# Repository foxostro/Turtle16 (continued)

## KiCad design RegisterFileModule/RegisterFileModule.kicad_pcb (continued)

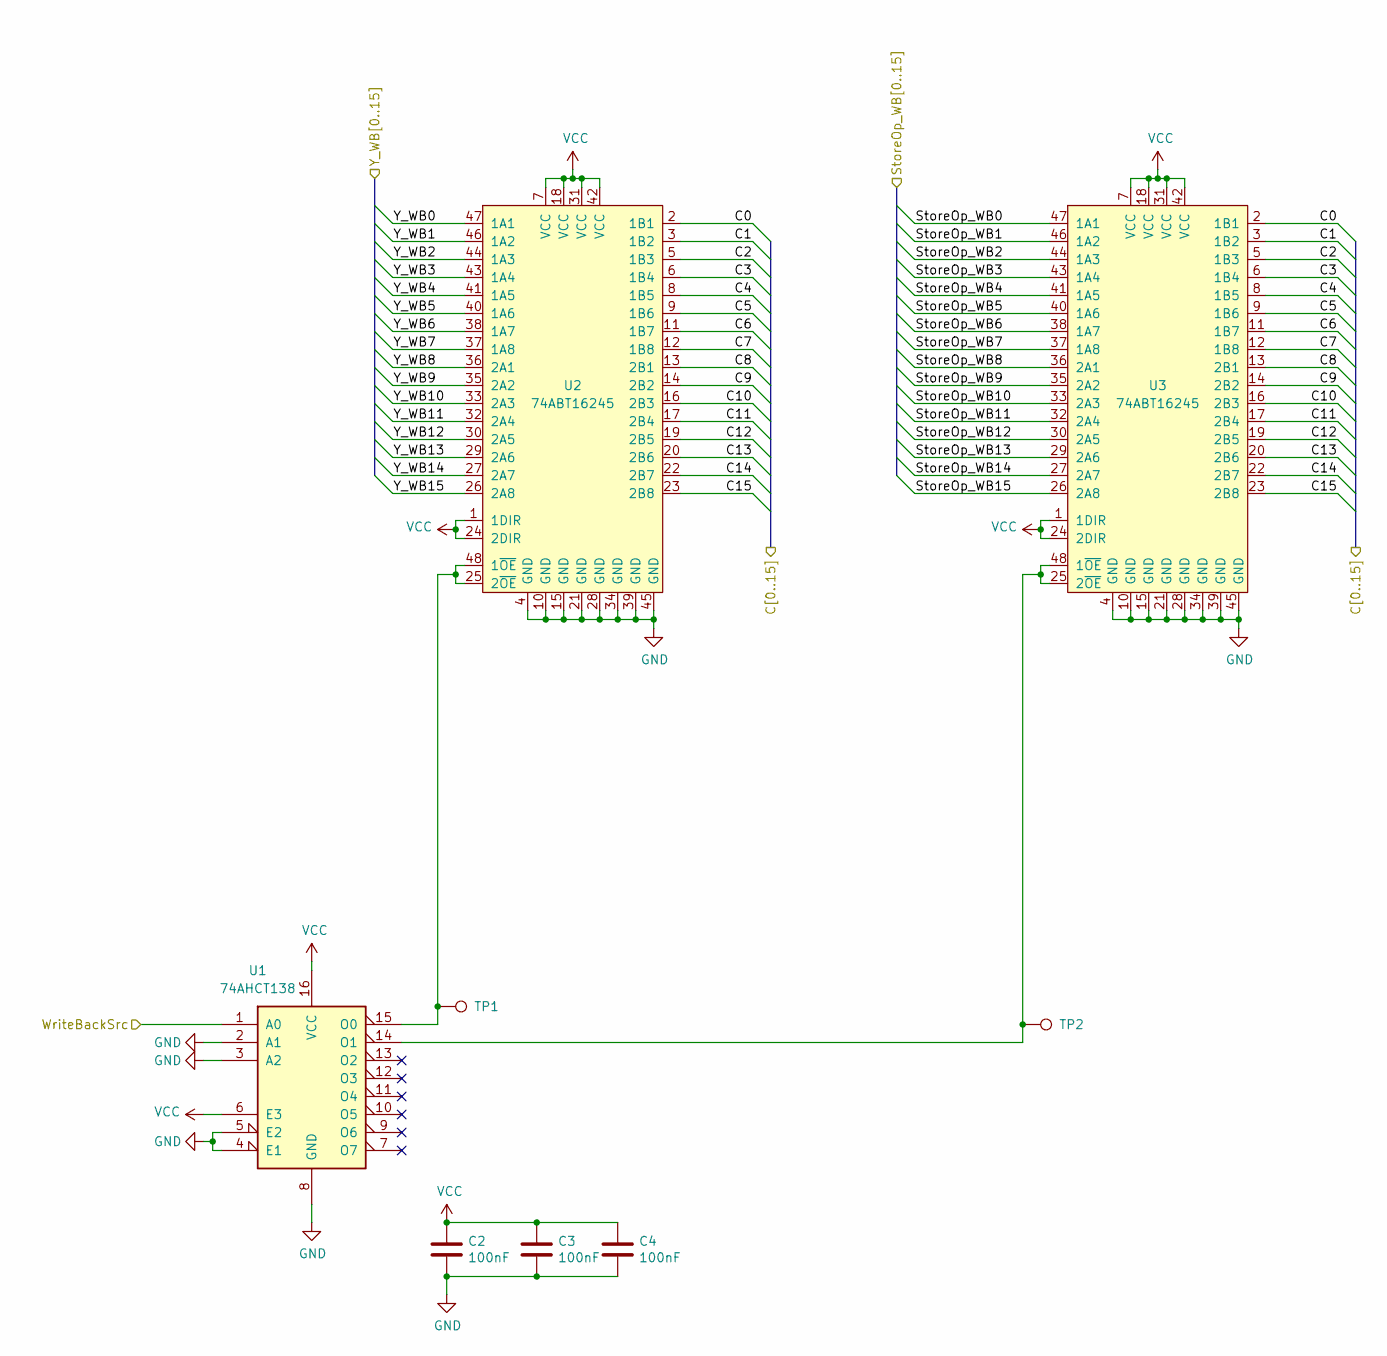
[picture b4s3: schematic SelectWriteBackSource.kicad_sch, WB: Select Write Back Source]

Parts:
C2, C3, C4: 100nF; C_0603_1608Metric_Pad1.08x0.95mm_HandSolder
TP1, TP2: TP; TestPoint_Pad_D1.0mm
U1: 74AHCT138; TSSOP-16_4.4x5mm_P0.65mm
U2, U3: 74ABT16245; TSSOP-48_6.1x12.5mm_P0.5mm

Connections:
/StoreOp_WB0: U3.47 (1A1); also elsewhere on the board
/StoreOp_WB1: U3.46 (1A2); also elsewhere on the board
/StoreOp_WB2: U3.44 (1A3); also elsewhere on the board
/StoreOp_WB3: U3.43 (1A4); also elsewhere on the board
/StoreOp_WB4: U3.41 (1A5); also elsewhere on the board
/StoreOp_WB5: U3.40 (1A6); also elsewhere on the board
/StoreOp_WB6: U3.38 (1A7); also elsewhere on the board
/StoreOp_WB7: U3.37 (1A8); also elsewhere on the board
/StoreOp_WB8: U3.36 (2A1); also elsewhere on the board
/StoreOp_WB9: U3.35 (2A2); also elsewhere on the board
/StoreOp_WB10: U3.33 (2A3); also elsewhere on the board
/StoreOp_WB11: U3.32 (2A4); also elsewhere on the board
/StoreOp_WB12: U3.30 (2A5); also elsewhere on the board
/StoreOp_WB13: U3.29 (2A6); also elsewhere on the board
/StoreOp_WB14: U3.27 (2A7); also elsewhere on the board
/StoreOp_WB15: U3.26 (2A8); also elsewhere on the board
/Write Back and Register File/Select Write Back Source/C0: U2.2 (1B1), U3.2 (1B1); also elsewhere on the board
/Write Back and Register File/Select Write Back Source/C1: U2.3 (1B2), U3.3 (1B2); also elsewhere on the board
/Write Back and Register File/Select Write Back Source/C2: U2.5 (1B3), U3.5 (1B3); also elsewhere on the board
/Write Back and Register File/Select Write Back Source/C3: U2.6 (1B4), U3.6 (1B4); also elsewhere on the board
/Write Back and Register File/Select Write Back Source/C4: U2.8 (1B5), U3.8 (1B5); also elsewhere on the board
/Write Back and Register File/Select Write Back Source/C5: U2.9 (1B6), U3.9 (1B6); also elsewhere on the board
/Write Back and Register File/Select Write Back Source/C6: U2.11 (1B7), U3.11 (1B7); also elsewhere on the board
/Write Back and Register File/Select Write Back Source/C7: U2.12 (1B8), U3.12 (1B8); also elsewhere on the board
/Write Back and Register File/Select Write Back Source/C8: U2.13 (2B1), U3.13 (2B1); also elsewhere on the board
/Write Back and Register File/Select Write Back Source/C9: U2.14 (2B2), U3.14 (2B2); also elsewhere on the board
/Write Back and Register File/Select Write Back Source/C10: U2.16 (2B3), U3.16 (2B3); also elsewhere on the board
/Write Back and Register File/Select Write Back Source/C11: U2.17 (2B4), U3.17 (2B4); also elsewhere on the board
/Write Back and Register File/Select Write Back Source/C12: U2.19 (2B5), U3.19 (2B5); also elsewhere on the board
/Write Back and Register File/Select Write Back Source/C13: U2.20 (2B6), U3.20 (2B6); also elsewhere on the board
/Write Back and Register File/Select Write Back Source/C14: U2.22 (2B7), U3.22 (2B7); also elsewhere on the board
/Write Back and Register File/Select Write Back Source/C15: U2.23 (2B8), U3.23 (2B8); also elsewhere on the board
/Write Back and Register File/WriteBackSrc: U1.1 (A0); also elsewhere on the board
/Y_WB0: U2.47 (1A1); also elsewhere on the board
/Y_WB1: U2.46 (1A2); also elsewhere on the board
/Y_WB2: U2.44 (1A3); also elsewhere on the board
/Y_WB3: U2.43 (1A4); also elsewhere on the board
/Y_WB4: U2.41 (1A5); also elsewhere on the board
/Y_WB5: U2.40 (1A6); also elsewhere on the board
/Y_WB6: U2.38 (1A7); also elsewhere on the board
/Y_WB7: U2.37 (1A8); also elsewhere on the board
/Y_WB8: U2.36 (2A1); also elsewhere on the board
/Y_WB9: U2.35 (2A2); also elsewhere on the board
/Y_WB10: U2.33 (2A3); also elsewhere on the board
/Y_WB11: U2.32 (2A4); also elsewhere on the board
/Y_WB12: U2.30 (2A5); also elsewhere on the board
/Y_WB13: U2.29 (2A6); also elsewhere on the board
/Y_WB14: U2.27 (2A7); also elsewhere on the board
/Y_WB15: U2.26 (2A8); also elsewhere on the board
GND: C2.2, C3.2, C4.2, U1.2 (A1), U1.3 (A2), U1.4 (E1), U1.5 (E2), U1.8 (GND), U2.4 (GND), U2.10 (GND), U2.15 (GND), U2.21 (GND), U2.28 (GND), U2.34 (GND), U2.39 (GND), U2.45 (GND), U3.4 (GND), U3.10 (GND), U3.15 (GND), U3.21 (GND), U3.28 (GND), U3.34 (GND), U3.39 (GND), U3.45 (GND); also elsewhere on the board
unnamed: TP2.1, U1.14 (O1), U3.25 (2~OE), U3.48 (1~OE)
VCC: C2.1, C3.1, C4.1, U1.6 (E3), U1.16 (VCC), U2.1 (1DIR), U2.7 (VCC), U2.18 (VCC), U2.24 (2DIR), U2.31 (VCC), U2.42 (VCC), U3.1 (1DIR), U3.7 (VCC), U3.18 (VCC), U3.24 (2DIR), U3.31 (VCC), U3.42 (VCC); also elsewhere on the board

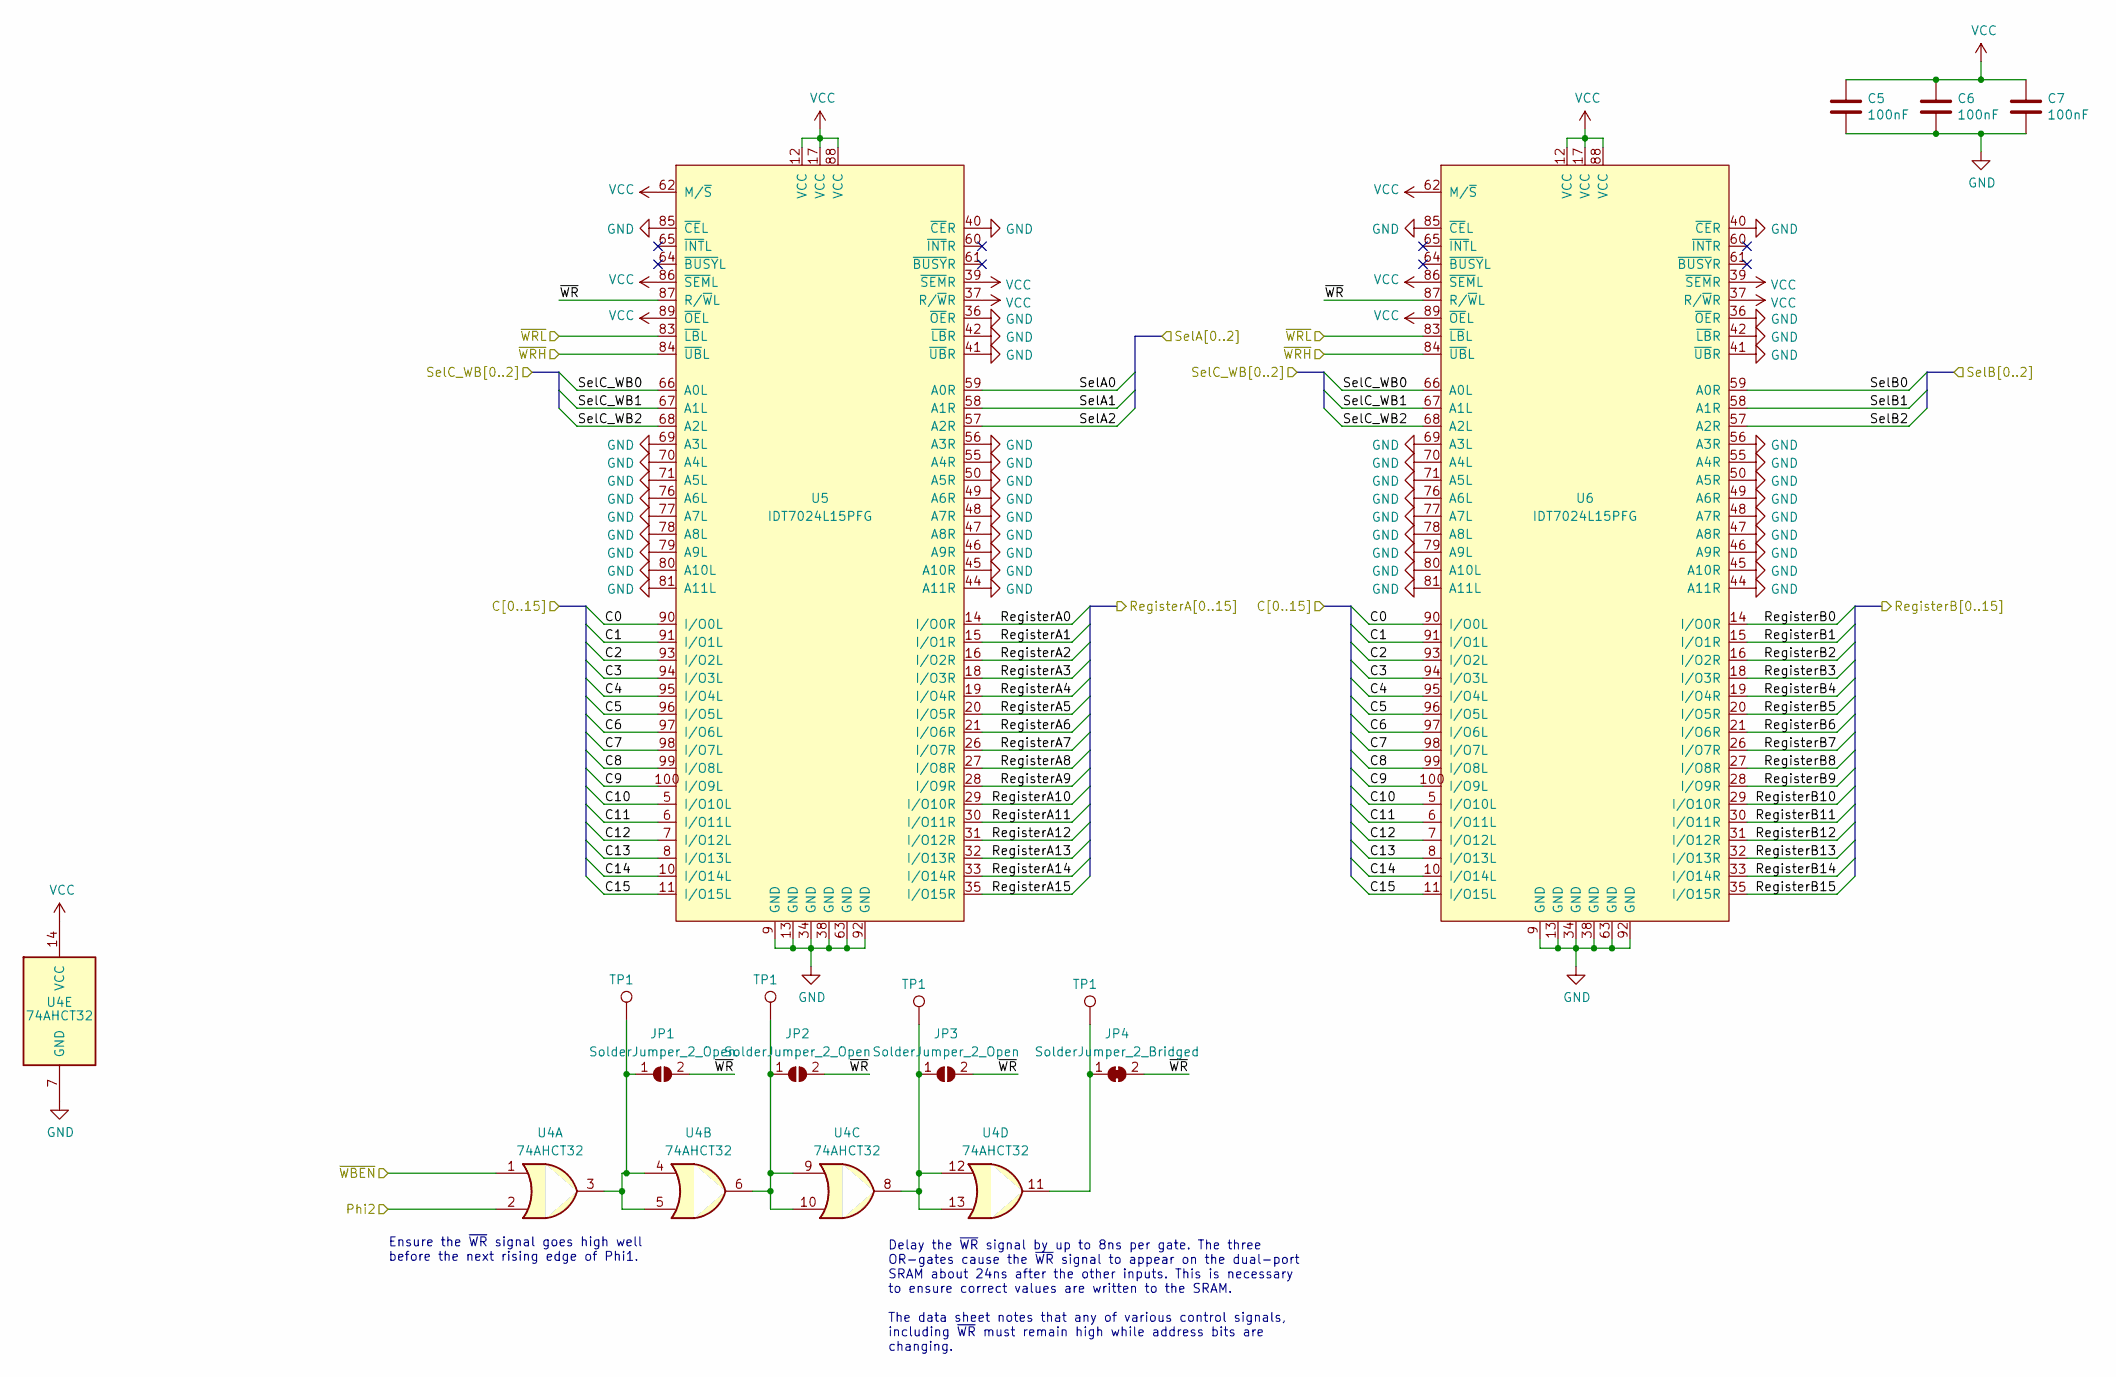
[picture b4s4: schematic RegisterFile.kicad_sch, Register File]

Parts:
C5, C6, C7: 100nF; C_0603_1608Metric_Pad1.08x0.95mm_HandSolder
JP1, JP2, JP3: SolderJumper_2_Open; SolderJumper-2_P1.3mm_Open_RoundedPad1.0x1.5mm
JP4: SolderJumper_2_Bridged; SolderJumper-2_P1.3mm_Bridged2Bar_RoundedPad1.0x1.5mm
TP1: TP; TestPoint_Pad_D1.0mm
U4: 74AHCT32; TSSOP-14_4.4x5mm_P0.65mm
U5, U6: IDT7024L15PFG; TQFP-100_14x14mm_P0.5mm

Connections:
/RegisterA0: U5.14 (I/O0R); also elsewhere on the board
/RegisterA1: U5.15 (I/O1R); also elsewhere on the board
/RegisterA2: U5.16 (I/O2R); also elsewhere on the board
/RegisterA3: U5.18 (I/O3R); also elsewhere on the board
/RegisterA4: U5.19 (I/O4R); also elsewhere on the board
/RegisterA5: U5.20 (I/O5R); also elsewhere on the board
/RegisterA6: U5.21 (I/O6R); also elsewhere on the board
/RegisterA7: U5.26 (I/O7R); also elsewhere on the board
/RegisterA8: U5.27 (I/O8R); also elsewhere on the board
/RegisterA9: U5.28 (I/O9R); also elsewhere on the board
/RegisterA10: U5.29 (I/O10R); also elsewhere on the board
/RegisterA11: U5.30 (I/O11R); also elsewhere on the board
/RegisterA12: U5.31 (I/O12R); also elsewhere on the board
/RegisterA13: U5.32 (I/O13R); also elsewhere on the board
/RegisterA14: U5.33 (I/O14R); also elsewhere on the board
/RegisterA15: U5.35 (I/O15R); also elsewhere on the board
/RegisterB0: U6.14 (I/O0R); also elsewhere on the board
/RegisterB1: U6.15 (I/O1R); also elsewhere on the board
/RegisterB2: U6.16 (I/O2R); also elsewhere on the board
/RegisterB3: U6.18 (I/O3R); also elsewhere on the board
/RegisterB4: U6.19 (I/O4R); also elsewhere on the board
/RegisterB5: U6.20 (I/O5R); also elsewhere on the board
/RegisterB6: U6.21 (I/O6R); also elsewhere on the board
/RegisterB7: U6.26 (I/O7R); also elsewhere on the board
/RegisterB8: U6.27 (I/O8R); also elsewhere on the board
/RegisterB9: U6.28 (I/O9R); also elsewhere on the board
/RegisterB10: U6.29 (I/O10R); also elsewhere on the board
/RegisterB11: U6.30 (I/O11R); also elsewhere on the board
/RegisterB12: U6.31 (I/O12R); also elsewhere on the board
/RegisterB13: U6.32 (I/O13R); also elsewhere on the board
/RegisterB14: U6.33 (I/O14R); also elsewhere on the board
/RegisterB15: U6.35 (I/O15R); also elsewhere on the board
/SelA0: U5.59 (A0R); also elsewhere on the board
/SelA1: U5.58 (A1R); also elsewhere on the board
/SelA2: U5.57 (A2R); also elsewhere on the board
/SelB0: U6.59 (A0R); also elsewhere on the board
/SelB1: U6.58 (A1R); also elsewhere on the board
/SelB2: U6.57 (A2R); also elsewhere on the board
/SelC_WB0: U5.66 (A0L), U6.66 (A0L); also elsewhere on the board
/SelC_WB1: U5.67 (A1L), U6.67 (A1L); also elsewhere on the board
/SelC_WB2: U5.68 (A2L), U6.68 (A2L); also elsewhere on the board
/Write Back and Register File/Phi2: U4.2; also elsewhere on the board
/Write Back and Register File/Select Write Back Source/C0: U5.90 (I/O0L), U6.90 (I/O0L); also elsewhere on the board
/Write Back and Register File/Select Write Back Source/C1: U5.91 (I/O1L), U6.91 (I/O1L); also elsewhere on the board
/Write Back and Register File/Select Write Back Source/C2: U5.93 (I/O2L), U6.93 (I/O2L); also elsewhere on the board
/Write Back and Register File/Select Write Back Source/C3: U5.94 (I/O3L), U6.94 (I/O3L); also elsewhere on the board
/Write Back and Register File/Select Write Back Source/C4: U5.95 (I/O4L), U6.95 (I/O4L); also elsewhere on the board
/Write Back and Register File/Select Write Back Source/C5: U5.96 (I/O5L), U6.96 (I/O5L); also elsewhere on the board
/Write Back and Register File/Select Write Back Source/C6: U5.97 (I/O6L), U6.97 (I/O6L); also elsewhere on the board
/Write Back and Register File/Select Write Back Source/C7: U5.98 (I/O7L), U6.98 (I/O7L); also elsewhere on the board
/Write Back and Register File/Select Write Back Source/C8: U5.99 (I/O8L), U6.99 (I/O8L); also elsewhere on the board
/Write Back and Register File/Select Write Back Source/C9: U5.100 (I/O9L), U6.100 (I/O9L); also elsewhere on the board
/Write Back and Register File/Select Write Back Source/C10: U5.5 (I/O10L), U6.5 (I/O10L); also elsewhere on the board
/Write Back and Register File/Select Write Back Source/C11: U5.6 (I/O11L), U6.6 (I/O11L); also elsewhere on the board
/Write Back and Register File/Select Write Back Source/C12: U5.7 (I/O12L), U6.7 (I/O12L); also elsewhere on the board
/Write Back and Register File/Select Write Back Source/C13: U5.8 (I/O13L), U6.8 (I/O13L); also elsewhere on the board
/Write Back and Register File/Select Write Back Source/C14: U5.10 (I/O14L), U6.10 (I/O14L); also elsewhere on the board
/Write Back and Register File/Select Write Back Source/C15: U5.11 (I/O15L), U6.11 (I/O15L); also elsewhere on the board
/Write Back and Register File/sheet60693B95/~WR: JP1.2 (B), JP2.2 (B), JP3.2 (B), JP4.2 (B), U5.87 (R/~WL), U6.87 (R/~WL)
/Write Back and Register File/~WBEN: U4.1; also elsewhere on the board
/Write Back and Register File/~WRH: U5.84 (~UBL), U6.84 (~UBL); also elsewhere on the board
/Write Back and Register File/~WRL: U5.83 (~LBL), U6.83 (~LBL); also elsewhere on the board
GND: C5.2, C6.2, C7.2, U4.7 (GND), U5.9 (GND), U5.13 (GND), U5.34 (GND), U5.36 (~OER), U5.38 (GND), U5.40 (~CER), U5.41 (~UBR), U5.42 (~LBR), U5.44 (A11R), U5.45 (A10R), U5.46 (A9R), U5.47 (A8R), U5.48 (A7R), U5.49 (A6R), U5.50 (A5R), U5.55 (A4R), U5.56 (A3R), U5.63 (GND), U5.69 (A3L), U5.70 (A4L), U5.71 (A5L), U5.76 (A6L), U5.77 (A7L), U5.78 (A8L), U5.79 (A9L), U5.80 (A10L), U5.81 (A11L), U5.85 (~CEL), U5.92 (GND), U6.9 (GND), U6.13 (GND), U6.34 (GND), U6.36 (~OER), U6.38 (GND), U6.40 (~CER), U6.41 (~UBR), U6.42 (~LBR), U6.44 (A11R), U6.45 (A10R), U6.46 (A9R), U6.47 (A8R), U6.48 (A7R), U6.49 (A6R), U6.50 (A5R), U6.55 (A4R), U6.56 (A3R), U6.63 (GND), U6.69 (A3L), U6.70 (A4L), U6.71 (A5L), U6.76 (A6L), U6.77 (A7L), U6.78 (A8L), U6.79 (A9L), U6.80 (A10L), U6.81 (A11L), U6.85 (~CEL), U6.92 (GND); also elsewhere on the board
VCC: C5.1, C6.1, C7.1, U4.14 (VCC), U5.12 (VCC), U5.17 (VCC), U5.37 (R/~WR), U5.39 (~SEMR), U5.62 (M/~S), U5.86 (~SEML), U5.88 (VCC), U5.89 (~OEL), U6.12 (VCC), U6.17 (VCC), U6.37 (R/~WR), U6.39 (~SEMR), U6.62 (M/~S), U6.86 (~SEML), U6.88 (VCC), U6.89 (~OEL); also elsewhere on the board

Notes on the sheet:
Delay the ~{WR} signal by up to 8ns per gate. The three OR-gates cause the ~{WR} signal to appear on the dual-port SRAM about 24ns after the other inputs. This is necessary to ensure correct values are written to the SRAM. The data sheet notes that any of various control signals, including ~{WR} mu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
Ensure the ~{WR} signal goes high well before the next rising edge of Phi1.

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
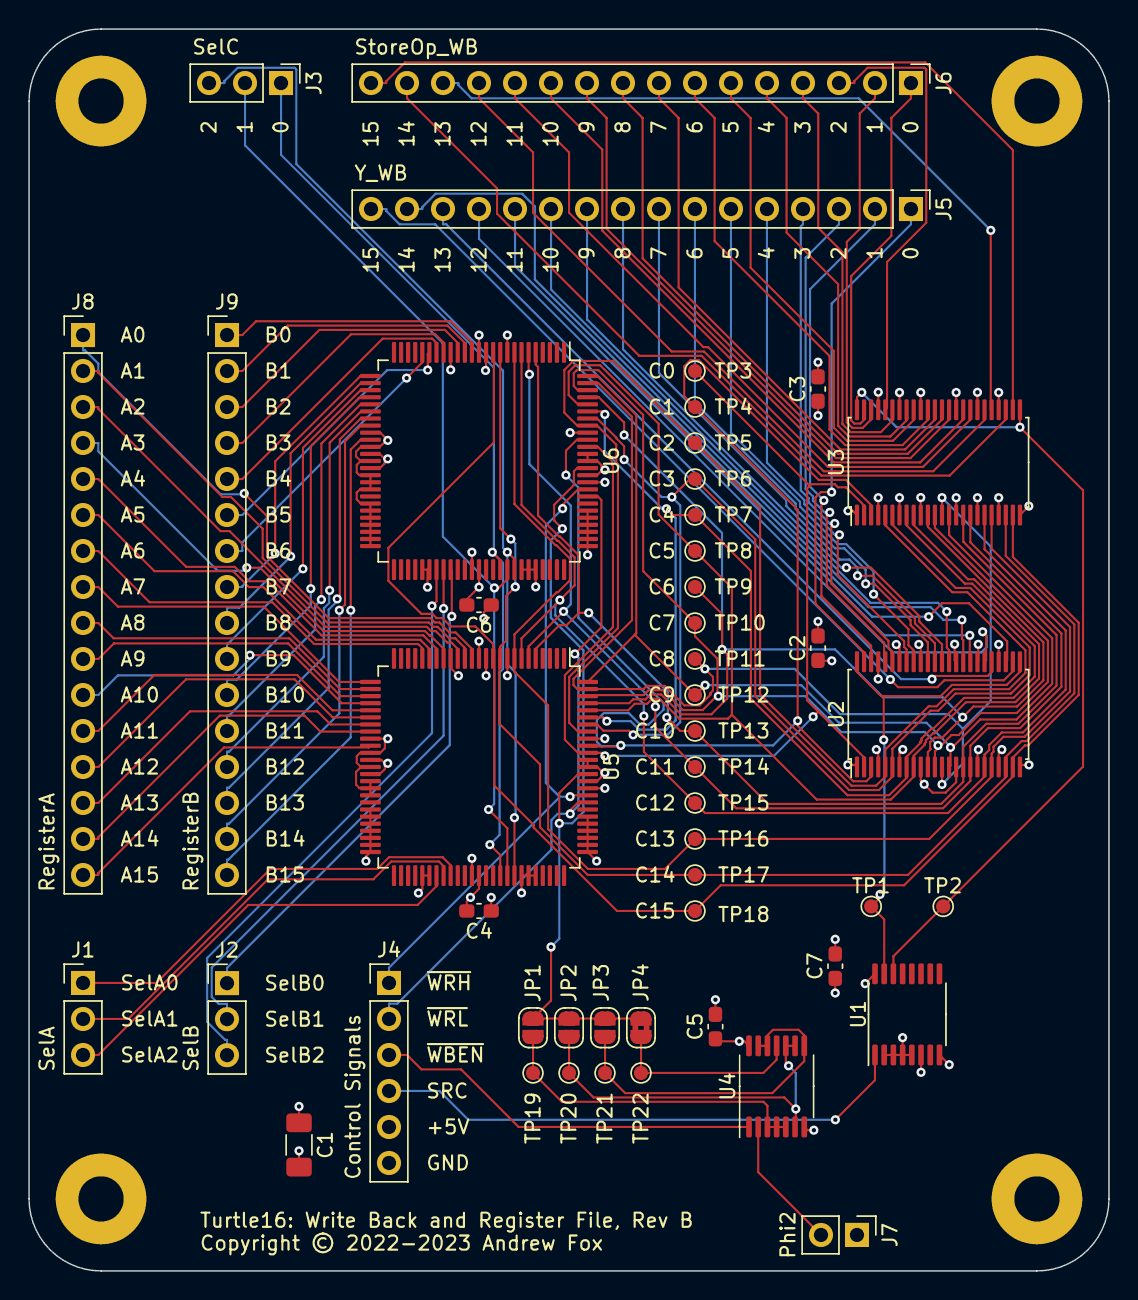
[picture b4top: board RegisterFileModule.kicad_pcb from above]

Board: 4 copper layers, 76.2 x 87.6 mm, 52 parts (0 on the bottom side), 103 nets.

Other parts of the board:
TP19, TP20, TP21, TP22: TP; TestPoint_Pad_D1.0mm
